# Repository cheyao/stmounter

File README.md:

# Cool stm32 dev board

Get this cheap and small stm32 dev board! it's a drop in replacement for a raspberry pi pico, so upgrade your device's performance at no cost!

It even supports USB, has 2 on-board LEDs and has multiple ADC channels! How awesome :D

### Features

It has a STM32F373CCT on it, which has:
- 256KB flash
- 72MHz
- 32 Bit
- ARM® Cortex®-M4
- USB support

Paired with this processor this dev board is:
- In a raspberry pi pico foorprint - direct replacement
- Duan oscillators, accurate RTC timing
- USB C!
- 2 user LEDs
- dual layer design - low fabrication cost

### Why?

Why use a stm32 instead of a raspberry pi2040? The STM32 chips are more powerful, has more dedicated i/o pins and USB support!

As you can see, almost all signal traces are routed on a single layer, thus preserving the maximal amount of signal integrity. The ground plane is also not slices up, sllowing direct current return paths.

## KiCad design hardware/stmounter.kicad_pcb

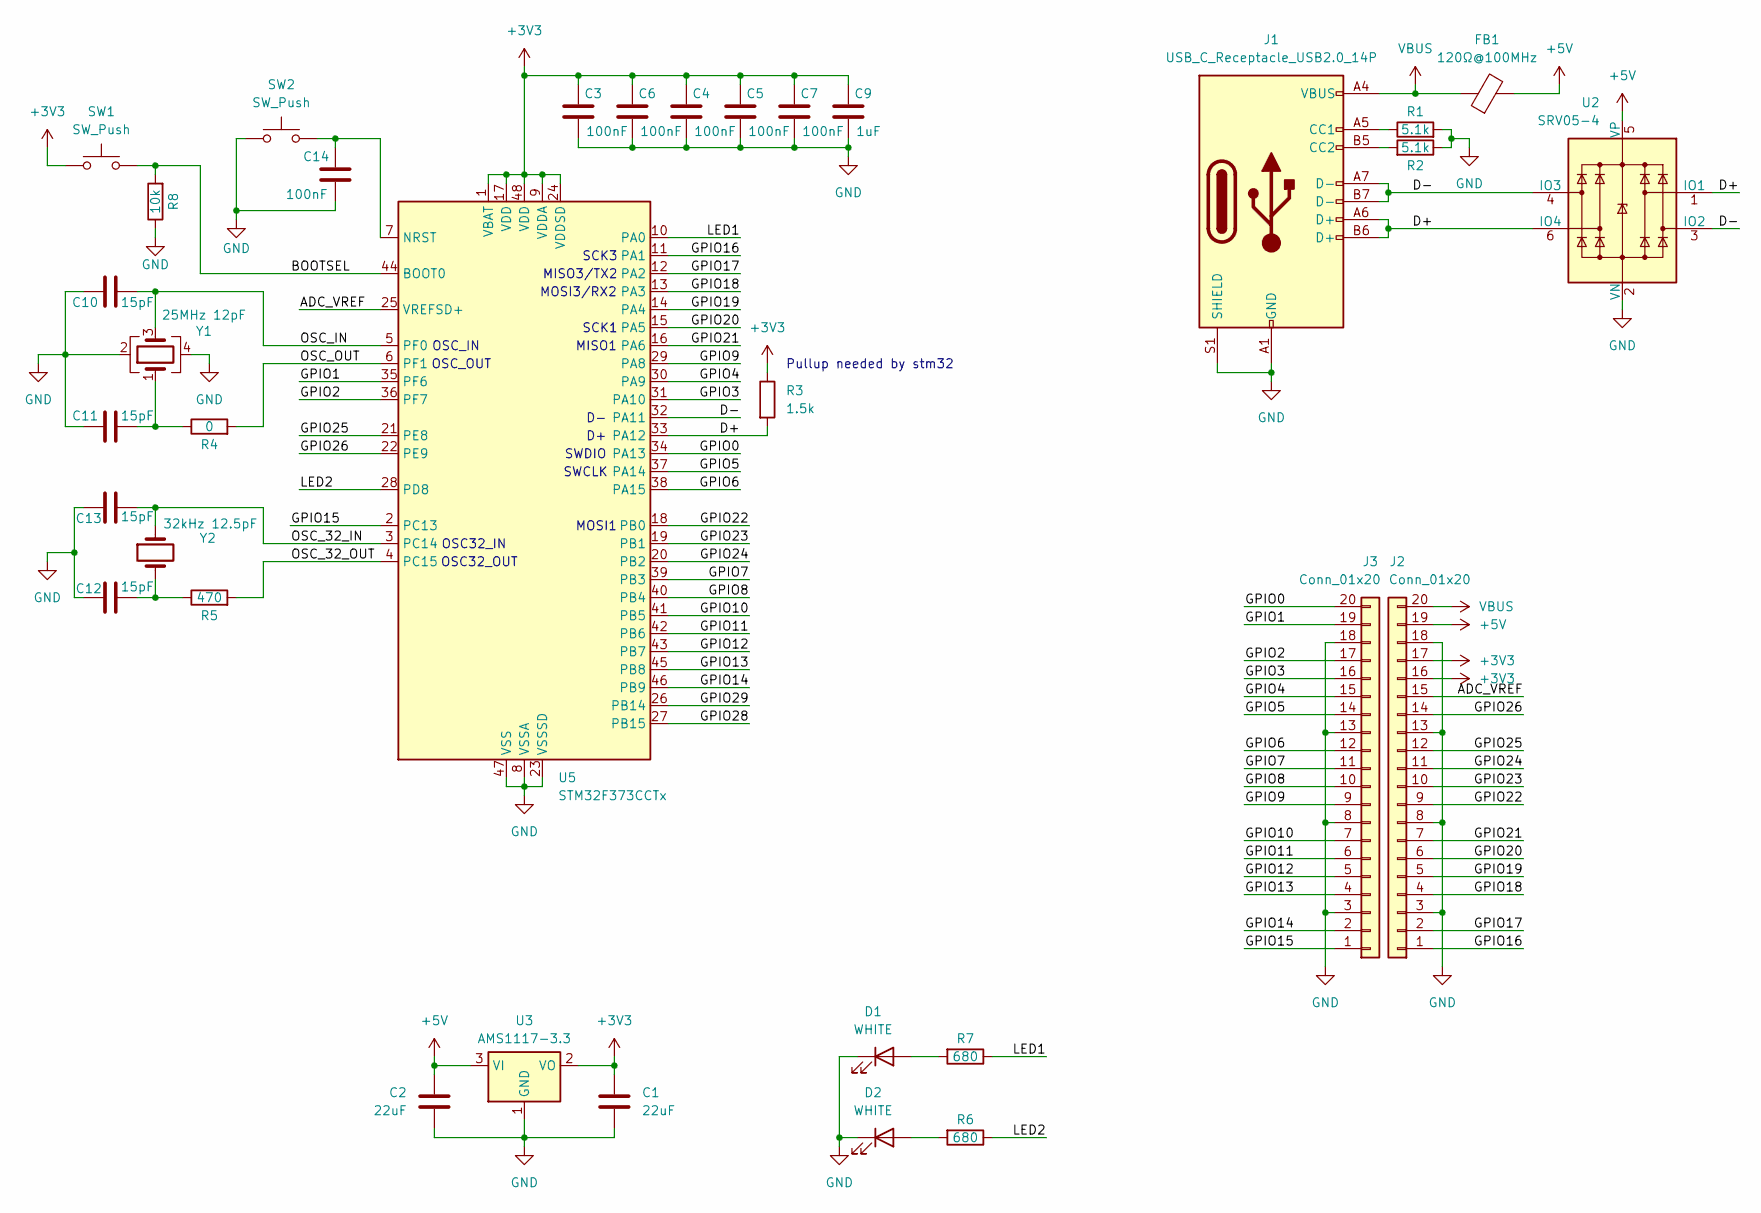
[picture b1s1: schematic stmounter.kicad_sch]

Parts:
C1, C2: 22uF; C_0603_1608Metric; LCSC Part # C59461
C3, C4, C5, C6, C7, C14: 100nF; C_0402_1005Metric; LCSC Part # C1525
C9: 1uF; C_0402_1005Metric; LCSC Part # C52923
C10, C11, C12, C13: 15pF; C_0402_1005Metric; LCSC Part # C1548
D1, D2: WHITE; LED_0603_1608Metric; LCSC Part # C2290
FB1: 120Ω@100MHz; L_0603_1608Metric; LCSC Part # C14709
J1: USB_C_Receptacle_USB2.0_14P; USB_C_Receptacle_GCT_USB4105-xx-A_16P_TopMnt_Horizontal; LCSC Part # C2765186
J2, J3: Conn_01x20; PinSocket_1x20_P2.54mm_Vertical
R1, R2: 5.1k; R_0402_1005Metric; LCSC Part # C25905
R3: 1.5k; R_0402_1005Metric; LCSC Part # C25867
R4: 0; R_0402_1005Metric; LCSC Part # C17168
R5: 470; R_0402_1005Metric; LCSC Part # C25117
R6, R7: 680; R_0402_1005Metric; LCSC Part # C25130
R8: 10k; R_0402_1005Metric; LCSC Part # C25744
SW1, SW2: SW_Push; TS-1088-AR02016-Switch-SMD; LCSC Part # C720477
U2: SRV05-4; SOT-23-6; LCSC Part # C7420376
U3: AMS1117-3.3; SOT-223-3_TabPin2; LCSC Part # C6186
U5: STM32F373CCTx; LQFP-48_7x7mm_P0.5mm; LCSC Part # C89403
Y1: 25MHz 12pF; Crystal_SMD_3225-4Pin_3.2x2.5mm; LCSC Part # C9006
Y2: 32kHz 12.5pF; Crystal_SMD_3215-2Pin_3.2x1.5mm; LCSC Part # C32346 (

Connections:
+3V3: C1.1, C3.1, C4.1, C5.1, C6.1, C7.1, C9.1, J2.16, J2.17, R3.1, SW1.1, U3.2 (VO), U5.1 (VBAT), U5.9 (VDDA), U5.17 (VDD), U5.24 (VDDSD), U5.48 (VDD)
+5V: C2.1, FB1.2, J2.19, U2.5 (VP), U3.3 (VI)
/ADC_VREF: J2.15, U5.25 (VREFSD+)
/BOOTSEL: R8.2, SW1.2, U5.44 (BOOT0)
/D+: J1.A6 (D+), J1.B6 (D+), R3.2, U2.1 (IO1), U2.6 (IO4), U5.33 (PA12)
/D-: J1.A7 (D-), J1.B7 (D-), U2.3 (IO2), U2.4 (IO3), U5.32 (PA11)
/GPIO0: J3.20, U5.34 (PA13)
/GPIO1: J3.19, U5.35 (PF6)
/GPIO2: J3.17, U5.36 (PF7)
/GPIO3: J3.16, U5.31 (PA10)
/GPIO4: J3.15, U5.30 (PA9)
/GPIO5: J3.14, U5.37 (PA14)
/GPIO6: J3.12, U5.38 (PA15)
/GPIO7: J3.11, U5.39 (PB3)
/GPIO8: J3.10, U5.40 (PB4)
/GPIO9: J3.9, U5.29 (PA8)
/GPIO10: J3.7, U5.41 (PB5)
/GPIO11: J3.6, U5.42 (PB6)
/GPIO12: J3.5, U5.43 (PB7)
/GPIO13: J3.4, U5.45 (PB8)
/GPIO14: J3.2, U5.46 (PB9)
/GPIO15: J3.1, U5.2 (PC13)
/GPIO16: J2.1, U5.11 (PA1)
/GPIO17: J2.2, U5.12 (PA2)
/GPIO18: J2.4, U5.13 (PA3)
/GPIO19: J2.5, U5.14 (PA4)
/GPIO20: J2.6, U5.15 (PA5)
/GPIO21: J2.7, U5.16 (PA6)
/GPIO22: J2.9, U5.18 (PB0)
/GPIO23: J2.10, U5.19 (PB1)
/GPIO24: J2.11, U5.20 (PB2)
/GPIO25: J2.12, U5.21 (PE8)
/GPIO26: J2.14, U5.22 (PE9)
/GPIO28: U5.27 (PB15)
/GPIO29: U5.26 (PB14)
/LED1: R7.1, U5.10 (PA0)
/LED2: R6.1, U5.28 (PD8)
/OSC_32_IN: C13.2, U5.3 (PC14), Y2.1
/OSC_32_OUT: R5.2, U5.4 (PC15)
/OSC_IN: C10.2, U5.5 (PF0), Y1.3
/OSC_OUT: R4.2, U5.6 (PF1)
GND: C1.2, C2.2, C3.2, C4.2, C5.2, C6.2, C7.2, C9.2, C10.1, C11.1, C12.1, C13.1, C14.2, D1.1 (K), D2.1 (K), J1.A1 (GND), J1.A12 (GND), J1.B1 (GND), J1.B12 (GND), J1.S1 (SHIELD), J2.3, J2.8, J2.13, J2.18, J3.3, J3.8, J3.13, J3.18, R1.2, R2.1, R8.1, SW2.1, U2.2 (VN), U3.1 (GND), U5.8 (VSSA), U5.23 (VSSSD), U5.47 (VSS), Y1.2, Y1.4
unnamed: C11.2, R4.1, Y1.1
unnamed: C12.2, R5.1, Y2.2
unnamed: D1.2 (A), R7.2
unnamed: D2.2 (A), R6.2
unnamed: J1.A5 (CC1), R1.1
unnamed: J1.B5 (CC2), R2.2
unnamed: C14.1, SW2.2, U5.7 (NRST)
VBUS: FB1.1, J1.A4 (VBUS), J1.A9 (VBUS), J1.B4 (VBUS), J1.B9 (VBUS), J2.20

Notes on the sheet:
OSC_IN
MISO1
SWCLK
MOSI1
Pullup needed by stm32
OSC32_IN
SWDIO
SCK1
SCK3
OSC32_OUT
OSC_OUT
MISO3/TX2
MOSI3/RX2

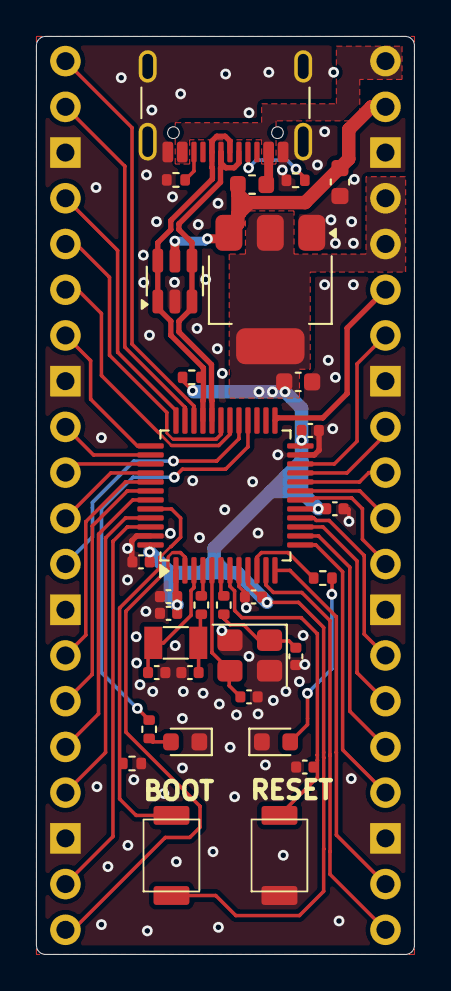
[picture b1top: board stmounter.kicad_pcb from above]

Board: 2 copper layers, 21.0 x 51.0 mm, 34 parts (0 on the bottom side), 48 nets.

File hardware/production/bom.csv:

Designator,Footprint,Quantity,Value,LCSC Part #
"C1, C2",0603,2,22uF,C59461 
"C10, C11, C12, C13",0402,4,15pF,C1548 
"C14, C3, C4, C5, C6, C7",0402,6,100nF,C1525 
C9,0402,1,1uF,C52923 
"D1, D2",0603,2,WHITE,C2290
FB1,0603,1,120Ω@100MHz,C14709
J1,USB_C_Receptacle_GCT_USB4105-xx-A_16P_TopMnt_Horizontal,1,USB_C_Receptacle_USB2.0_14P,C2765186
"R1, R2",0402,2,5.1k,C25905 
R3,0402,1,1.5k,C25867 
R4,0402,1,0,C17168
R5,0402,1,470,C25117 
"R6, R7",0402,2,680,C25130
R8,0402,1,10k,C25744 
"SW1, SW2",TS-1088-AR02016-Switch-SMD,2,SW_Push,C720477
U2,SOT-23-6,1,SRV05-4,C7420376 
U3,SOT-223-3_TabPin2,1,AMS1117-3.3,C6186
U5,LQFP-48_7x7mm_P0.5mm,1,STM32F373CCTx,C89403
Y1,Crystal_SMD_3225-4Pin_3.2x2.5mm,1,25MHz 12pF,C9006
Y2,Crystal_SMD_3215-2Pin_3.2x1.5mm,1,32kHz 12.5pF,C32346 (

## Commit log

2025-05-23 Init
2025-05-24 Progress
2025-05-27 Finalize pcb
2026-01-22 Fix broken CDN links
